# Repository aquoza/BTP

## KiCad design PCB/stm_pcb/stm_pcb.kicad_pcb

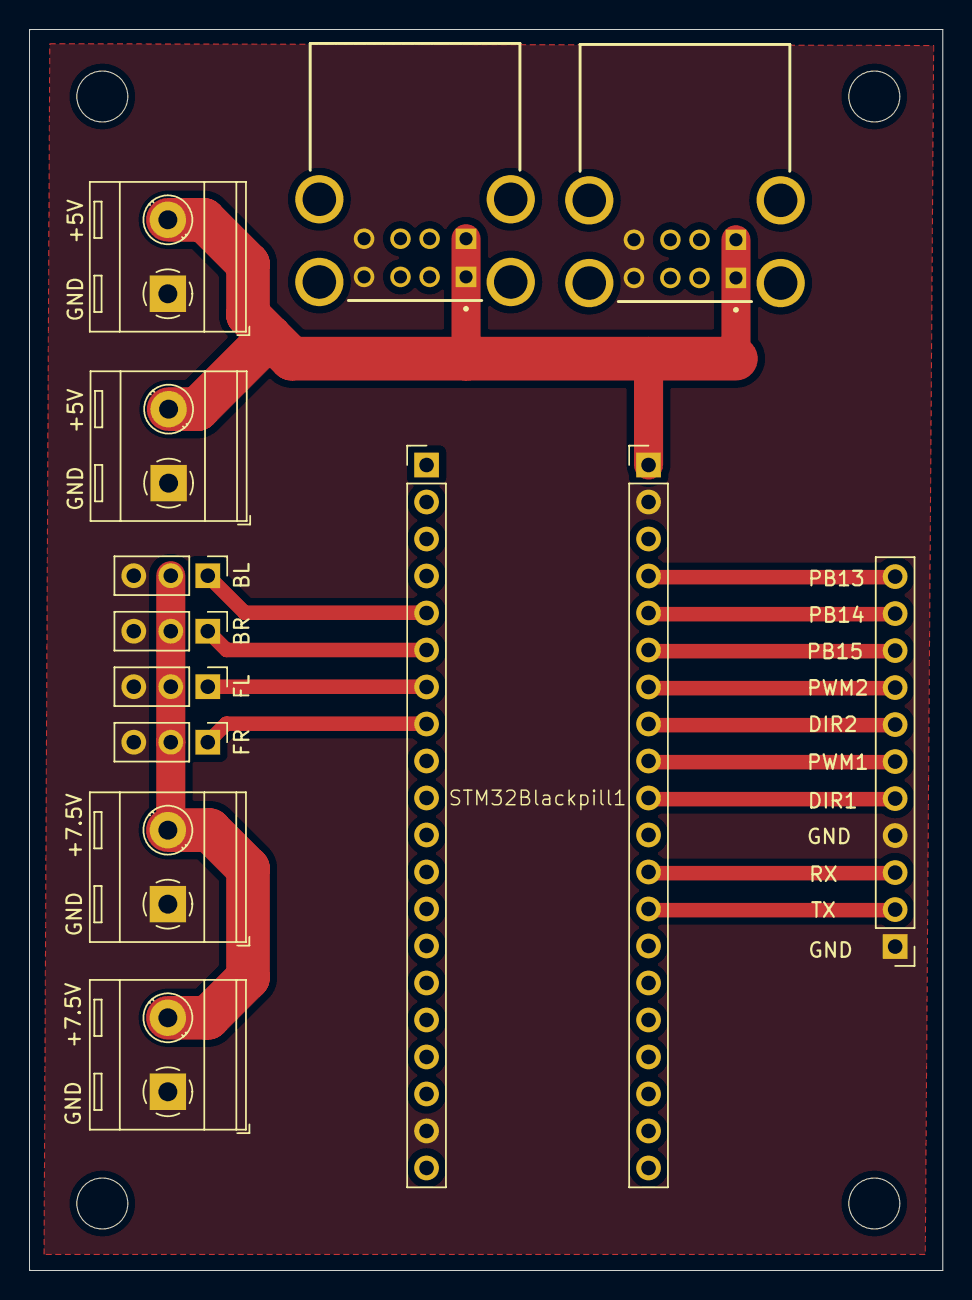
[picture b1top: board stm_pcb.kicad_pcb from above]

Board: 2 copper layers, 62.7 x 85.2 mm, 16 parts (0 on the bottom side), 16 nets.

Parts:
BL: Conn_01x03; PinHeader_1x03_P2.54mm_Vertical
BR: Conn_01x03; PinHeader_1x03_P2.54mm_Vertical
FL: Conn_01x03; PinHeader_1x03_P2.54mm_Vertical
FR: Conn_01x03; PinHeader_1x03_P2.54mm_Vertical
H1, H2, H3, H4: MountingHole; MountingHole_3.5mm
J1, J9: 5V; TerminalBlock_RND_205-00287_1x02_P5.08mm_Horizontal
J2, J12: 7V; TerminalBlock_RND_205-00287_1x02_P5.08mm_Horizontal
J10: Conn_01x11; PinHeader_1x11_P2.54mm_Vertical
STM32Blackpill1: Blackpill
USB1, USB2: USB; DualUSB

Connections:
+5V: J1.2, J9.2, STM32Blackpill1.5V (+5V), USB1.A01 (VCC1), USB1.B01 (VCC2), USB2.A01 (VCC1), USB2.B01 (VCC2)
+7.5V: BL.2, BR.2, FL.2, FR.2, J2.2, J12.2
DIR1: J10.5, STM32Blackpill1.DIR1
DIR2: J10.7, STM32Blackpill1.DIR2
GND: BL.3, BR.3, FL.3, FR.3, J1.1, J2.1, J9.1, J10.1, J10.4, J12.1, STM32Blackpill1.GND, USB1.A04 (GND1), USB1.B04 (GND2), USB2.A04 (GND1), USB2.B04 (GND2)
PB13: J10.11, STM32Blackpill1.PB13
PB14: J10.10, STM32Blackpill1.PB14
PB15: J10.9, STM32Blackpill1.PB15
PWM1: J10.6, STM32Blackpill1.PWM1
PWM2: J10.8, STM32Blackpill1.PWM2
RX: J10.3, STM32Blackpill1.RX
SERVOBL: BL.1, STM32Blackpill1.SERVOBL
SERVOBR: BR.1, STM32Blackpill1.SERVOBR
SERVOFL: FL.1, STM32Blackpill1.SERVOFL
SERVOFR: FR.1, STM32Blackpill1.SERVOFR
TX: J10.2, STM32Blackpill1.TX

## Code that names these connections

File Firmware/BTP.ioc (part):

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Mcu.Name=STM32F401C(B-C)Ux
Mcu.Package=UFQFPN48
Mcu.UserName=STM32F401CCUx
PA10.GPIOParameters=GPIO_Label
PA10.GPIO_Label=ServoFL
PA10.Signal=S_TIM1_CH3
PA11.GPIOParameters=GPIO_Label
PA11.GPIO_Label=ServoFR
PA11.Signal=S_TIM1_CH4
PA13.Mode=Trace_Asynchronous_SW
PA13.Signal=SYS_JTMS-SWDIO
PA14.Mode=Trace_Asynchronous_SW
PA14.Signal=SYS_JTCK-SWCLK
PA2.Mode=Asynchronous
PA2.Signal=USART2_TX
PA3.Mode=Asynchronous
PA3.Signal=USART2_RX
PA5.GPIOParameters=GPIO_Label
PA5.GPIO_Label=DIR1
PA5.Signal=GPIO_Output
PA6.GPIOParameters=GPIO_Label
PA6.GPIO_Label=PWM1
PA6.Signal=S_TIM3_CH1
PA7.GPIOParameters=GPIO_Label
PA7.GPIO_Label=DIR2
PA7.Signal=GPIO_Output
PA8.GPIOParameters=GPIO_Label
PA8.GPIO_Label=ServoBL
PA8.Signal=S_TIM1_CH1
PA9.GPIOParameters=GPIO_Label
PA9.GPIO_Label=ServoBR
PA9.Signal=S_TIM1_CH2
PB0.Signal=S_TIM3_CH3
PB13.Signal=GPIO_Output
PB14.Signal=GPIO_Output
PB15.Signal=GPIO_Output
PB3.Mode=Trace_Asynchronous_SW
PB3.Signal=SYS_JTDO-SWO
PH0\ -\ OSC_IN.Mode=HSE-External-Oscillator
PH0\ -\ OSC_IN.Signal=RCC_OSC_IN
PH1\ -\ OSC_OUT.Mode=HSE-External-Oscillator
PH1\ -\ OSC_OUT.Signal=RCC_OSC_OUT
RCC.HSE_VALUE=25000000
RCC.SYSCLKFreq_VALUE=16000000
board=custom

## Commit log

2025-01-24 init
